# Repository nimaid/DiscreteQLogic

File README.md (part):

# DiscreteQLogic
My resources and projects relating to digital circuits made out of discrete transistors.

## Efficient Discrete NMOS Logic Gate Designs
I have yet to find a well-compiled source that lists the most efficient NMOS implementations using discrete MOSFETS and resistors. This is likely because, well, it's a very slow and outdated technology that draws more power than CMOS.

However, for DIY projects where one wishes to do the bare minimum of soldering, layout, and purchasing, NMOS provides very good functionality at about half the transistor count of CMOS (at the expense of adding some resistors). Therefore, I have decided to use NMOS for my DIY projects, and as such, I have been collecting the most efficient gate designs, which use fewest transistors and resistors possible.

*(I have been making a library of these parts for both Digital and LTspice, in order to simulate them before building them. You can find these libraries in their respective subfolders of this repository.)*

For this list, I will use some shorthand notation to refer to the total transistor and resistor counts for each part. This shorthand will follow the format `xQyR`, where `x` is the total transistor count and `y` is the total resistor count. So, for example, an XOR gate which was labeled `6Q3R` would require 6 transistors and 3 resistors to build.

Sometimes, you may see the part count listed in the format `(!aQbR/xQyR)`. This means the simplest (lowest part count) version of the part has it's input(s) or output(s) inverted (the `!` means `NOT` or inversion). *This inverted version uses `a` transistors and `b` resistors.* In order to use the part in it's non-inverted state, one or more NOT gates is needed, which increases the total component count per part. *This non-inverted version uses `x` transistors and `y` resistors.* If you are using many of these parts with a shared signal on their inputs (like a clock), it is more economical to invert that signal *once* before it then goes into each of the inverted variants of the part. In addition, sometimes you get inverted outputs for free (like with latches and flip-flops), so you actually don't even need NOT gates a lot of the time! This can save a *TON* of components when building things like multi-bit registers or enablers, where the savings add up with more bits.

Unless otherwise stated, all transistors are N-type.

Resistor values should be chosen based on acceptable power dissipation and speed requirements. If the resistors are large (on the order of 10kΩ+), then power dissipation will be very low (the resistor lets less current through to ground), but the response time of the gate will be much slower. This is due to an inherent weakness in NMOS where it takes longer to charge up the combined gate capacitance of the MOSFETs and the stray capacitance in the wires though a larger resistor. Conversely, smaller values will yield higher power usage, but faster response times.

### NOT (1Q1R)
<details>
<summary>Details</summary>

The simplest gate to construct is a NOT gate (also known as an inverter). This is simply a pullup resistor with a transistor configured to short the output to ground when voltage is applied to it's gate. Make sure you understand how this gate works, because this fundamental principal is the foundation which allows the systematic construction of every other NMOS gate.

</details>

#### This section must be re-written.
<details>
<summary>Show it to me anyway!</summary>

### NAND (2Q1R)
<details>
<summary>Details</summary>

The next step up in complexity is the NAND gate. This is essentially just a NOT gate with an extra transistor in series to ground. This has the effect of only shorting the output to ground if *both* transistors are conducting. This results in the behavior of a NAND gate.

</details>

### NOR (2Q1R)
<details>
<summary>Details</summary>

The NOR gate is almost exactly the same as the NAND gate, except the second transistor is connected in parallel as opposed to series. This has the effect of shorting the output to ground if *either* transistors are conducting. This results in the behavior of a NOR gate.

</details>

### n-way NAND and NOR (\{n\}Q1R)
<details>
<summary>Details</summary>

It is possible to efficiently make NAND and NOR gates that have more than 2 inputs without chaining together the above units. This method uses fewer transistors and resistors than simply chaining the 2-way gates together. We do this be applying the same logic that took us from a 1-way NOT gate to 2-way NAND and NOR gates, but instead of putting only 2 transistors in either series or parallel, we put `n` transistors, where `n` is the number of inputs we want.

Here is an 8-way NAND gate.

Here is an 8-way NOR gate.

</details>

### AND and OR (3Q2R)
<details>
<summary>Details</summary>

The best way to make AND and OR gates happens to be the most straightforward. All we have to do is add a NOT gate after the NAND and NOR gates, as shown.

AND:

OR:

</details>

### AOI[a-b-...] (\{a + b + ...\}Q1R)
<details>
<summary>Details</summary>

The AOI (And-Or-Invert) gate is a bit unusual at first glance, and it is not as well known as the other gates. However, it is essential for building efficient NMOS circuits. This gate acts on "sets" of inputs, and processes them as follows:
- It first runs each "set" of inputs through an `n`-way AND gate, where `n` is the number of inputs in that set.
- The results from all of the AND gates are run through an `m`-way OR gate, where `m` is the number of sets.
- Finally, the output of the OR gate is run through a NOT gate (also called an inverter).

AOI gates are defined by a series of numbers, which specify exactly how many sets of inputs there are, and how many inputs are in each set. Each set can have a different number of inputs, and you can have an many sets as you like. This is in the format `a-b-c-...`, where `a`, `b`, `c`, etc. specify how many inputs each set has, in order. So a `2-3-1` AOI gate would have 3 sets with 2 inputs going to the first AND gate, 3 inputs going to the second AND gate, and the third set has only 1 input that goes directly to the OR gate stage (because AND only makes sense with 2 or more inputs).

Here is an example of an AOI2-2 gate using conventional combinational logic.

So why do we care about this odd gate as a single unit? Why don't we just use combinations of AND and NOR gates whenever we need to do these types of operations? The answer is that all of these logical operations can be easily implemented in a single NMOS logic block that uses far fewer transistors and resistors to achieve the same behavior.

Here is that same AIO2-2 gate in NMOS logic, using 4Q1R.

The way this works is actually very clever. First, observe that this is still arranged with a pullup resistor and transistors that, with some combinations of inputs, shorts to ground. This is the same idea as the NOT gate, and this is where the "inversion" comes from.

Second, observe that there are 2 parallel paths to ground, just like the NOR gate. The only difference is that instead of a single transistor, each path has 2 transistors in series, which is exactly the same method used to construct the NAND gate. Indeed, when either set of series transistors is conducting, the output will be shorted to ground, providing the AND functionality for each set.

Finally, observe that because the sets of series transistors are in parallel with each other, the compound effect of ORing the results of the 2 AND operations is realized.

Here is an example of a 2-1 AOI gate.

And just to make sure it makes sense, here is a 2-2-2-2 AOI gate.

As you can see, you can customize the number of sets and their respective input count to fit your specific needs in the same way you can customize the number of inputs to a NAND or NOR gate.

The final transistor count of each AOI gate will be exactly equal to the total number of inputs, and each AOI gate will only ever use a single resistor.

</details>

### XOR (6Q3R)
<details>
<summary>Details</summary>

It is possible to use an AOI2-2 gate and 2 NOT gates to make an extremely elegant XOR gate, as shown below.

To understand why this works, think about the AOI gate as "a gate that will set it's output to 0 only when a set of inputs is all 1". In this way, we can analyze the truth table of the XOR gate to find which input conditions result in a 0 and test for them with sets of AND gates that have their inputs set to 1 in those conditions.

XOR gate truth table:
```
┌───┬───┬─────┐
│ A │ B │ Out │
╞═══╪═══╪═════╡
│ 0 │ 0 │  0  │
├───┼───┼─────┤
│ 0 │ 1 │  1  │
├───┼───┼─────┤
│ 1 │ 0 │  1  │
├───┼───┼─────┤
│ 1 │ 1 │  0  │
└───┴───┴─────┘
```

We can see that the output is only 0 when both inputs are the same. Therefore, the first AND gate in the AOI2-2 is fed with both inputs directly, so that the output will go to 0 when both inputs are 1. Next, we need the output to also be 0 when both inputs are 0, and we can do this by simply inverting both inputs before feeding them into the second AND gate. Now we have a gate that outputs 0 when the inputs are either both 1 or both 0, and outputs 1 otherwise. This is an XOR gate!

</details>

### XNOR (6Q3R)
<details>
<summary>Details</summary>

We can implement the XNOR gate without using the classic XOR + NOT gate setup. To do so, we simply re-order the NOT gates in our XOR gate design so that the output goes to 0 in each case where the inputs are different, as opposed to the same.

</details>

### Enabler / 3-State Driver (!5Q1R/6Q2R)
<details>
<summary>Details</summary>

This component is a bit unique, as it is the only one which *requires* a few P-channel MOSFETs in addition to N-channel ones. This circuit takes 2 inputs, `In` (input) and `en` (enable). When `en` is 1, the output is equal to `In`. However, when `en` is 0, the output is in a state known as "high impedance". This is a state that is neither a 0 (ground) or 1 (VCC), but instead the output is electrically disconnected entirely.

This is extremely useful when you want to have 2 signals occupy the same wire at different times (the most common example being a data bus inside a computer). To understand the reason why we need a special part for this, lets take an example case where we connect the outputs of 2 AND gates to each other directly. If the first was outputting 1 (VCC) and the second was outputting 0 (ground), then there would be a short-circuit through that wire and those 2 AND gates, which would cause the device to malfunction and likely sustain damage. By putting enablers between the outputs and their shared wire, and by *only enabling a single output at a time*, you can avoid such a disaster.

Before showing you the enabler circuit, it will be useful to first understand how a CMOS-based NOT gate works:

The top transistor is P-channel, and the bottom one is N-channel. In the configuration shown, the N-channel MOSFET will conduct (to ground) when VCC (1) is applied to it's gate, and will act like an open switch when it is grounded (0). This works just like in the N-channel NOT gate. However, the P-channel MOSFET behaves in exactly the opposite way. When VCC (1) is applied to it's gate, it acts like an open switch, and it conducts (to VCC) when the gate is grounded (0).

With this understanding, we can see that when `In` is 0, the upper P-channel MOSFET will be conducting to VCC (1), and the lower N-channel MOSFET will be disconnected, resulting in `Out` being only connected to VCC, and therefore a 1. Conversely, when `In` is 1, the P-channel MOSFET will be open and the N-channel one will be conducting to ground, therefore resulting in a 0. This is the fundamental idea behind CMOS, and it is used in the construction of the enabler circuit.

Now, we are ready to look at the *inverted* enabler circuit (5Q1R):

The top 2 transistors are P-channel, while the lower two are N-channel. *(This means the circuit uses 3 N-channel MOSFETs and 2 P-channel MOSFETs.)*

First, note how to topmost (P-channel) and bottommost (N-channel) MOSFETs both have their gates connected directly to `In`, just like the CMOS NOT gate. This means that if those other 2 MOSFETs weren't in the way, this circuit would actually *be* a CMOS NOT gate, and would therefore just invert the input signal. (Out = !In) Alone this isn't very special, but those 2 MOSFETs in the middle which seperate these ones from `Out` are what actually make this circuit useful as an enabler.

Those 2 middle MOSFETs are also a P-channel/N-channel pair, but with a single critical change from the CMOS NOT gate. Instead of both of their gates being directly connected, the upper-middle P-channel MOSFET has it's gate input inverted by a NOT gate. This means that when `en` is 1, *both* MOSFETs will conduct, but when `In` is 0, *neither* MOSFET will conduct (both act like an open switch). This means that when `en` is 1, the effect of the topmost and bottommost MOSFETs are uninterrupted and `Out` is equal to `!In`. However, when `en` is 0, `Out` is completely disconnected from both VCC and ground, *regardless* of the state of topmost and bottommost MOSFETs. This results in the desired behavior of an enabler, but with the input inverted.

In situations where an inverted input signal is already available without adding a NOT gate (like the inverted output on a latch or flip-flop), you can simply use this inverted version of the enabler and remove a few components from the design. However, there are often times where you can' get away with that, and absolutely need an enabler with a non-inverted input. In these situations, you have to bite the bullet and add a NOT gate, as shown below.

Non-inverted Enabler (6Q2R):

</details>

### Multiplexer (!5Q2R/6Q3R) [WIP] 
<details>
<summary>Details</summary>

[TODO: Explain the MUX API and why it is useful for routing signals.]

This functionality can be accomplished with the following combinational logic:

[TODO: Explain how the AND gates only allow the respective `In` signal through if the other input to the AND gate is on. Explain that because of the NOT gate, only 1 of the AND gates will allow it's signal to pass to the OR gate, effectively discarding the signal not selected by `sel`. Note how because only 1 signal is let through, the output of the OR gate will be equal to the selected signal, which is the desired behavior.]

Here is an efficient implementation of a multiplexer *with an inverted output* using an AOI2-2 gate (5Q2R):

Note that the AOI2-2 gate is almost exactly what we nee to replace the 2 AND gates and 1 OR gate. The only issue is that the output of the OR gate is inverted. Sometimes you can leverage the inverting nature of this circuit to avoid using a NOT gate to invert the inputs/output. However, if you need a non-inverting multiplexer, you must use a NOT gate on the output, as shown (6Q3R):

</details>

### Demultiplexer (!5Q3R/6Q4R) [WIP]
<details>
<summary>Details</summary>

[TODO]

[TODO]

[TODO]

</details>

### RS Latch and SR Latch (4Q2R) [WIP]
<details>
<summary>Details</summary>

The RS latch is the basic form of memory. [TODO: Add API definition and explain why it's useful.]

RS Latch Diagram:

[TODO: Add a breakdown of why it works, step-by step. Also explain metastable (invalid) configurations. Also explain that the circuit starts up in a "random" state.]

Here is the RS latch in the logic simulator, using our NMOS components:

The SR latch is very similar to the RS latch, but it is made of NAND gates instead of NOR gates. In addition, it's inputs are both inverted (active low) and flipped (set on top and reset on bottom). [TODO: Add full API definition and explain why it's useful, especially compared to the RS latch. Note now the inverted inputs are actually useful later on.]

SR Latch Diagram:

[TODO: Add a step-by-step breakdown that references the RS latch breakdown. Explain that this also starts up in a "random" state.]

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
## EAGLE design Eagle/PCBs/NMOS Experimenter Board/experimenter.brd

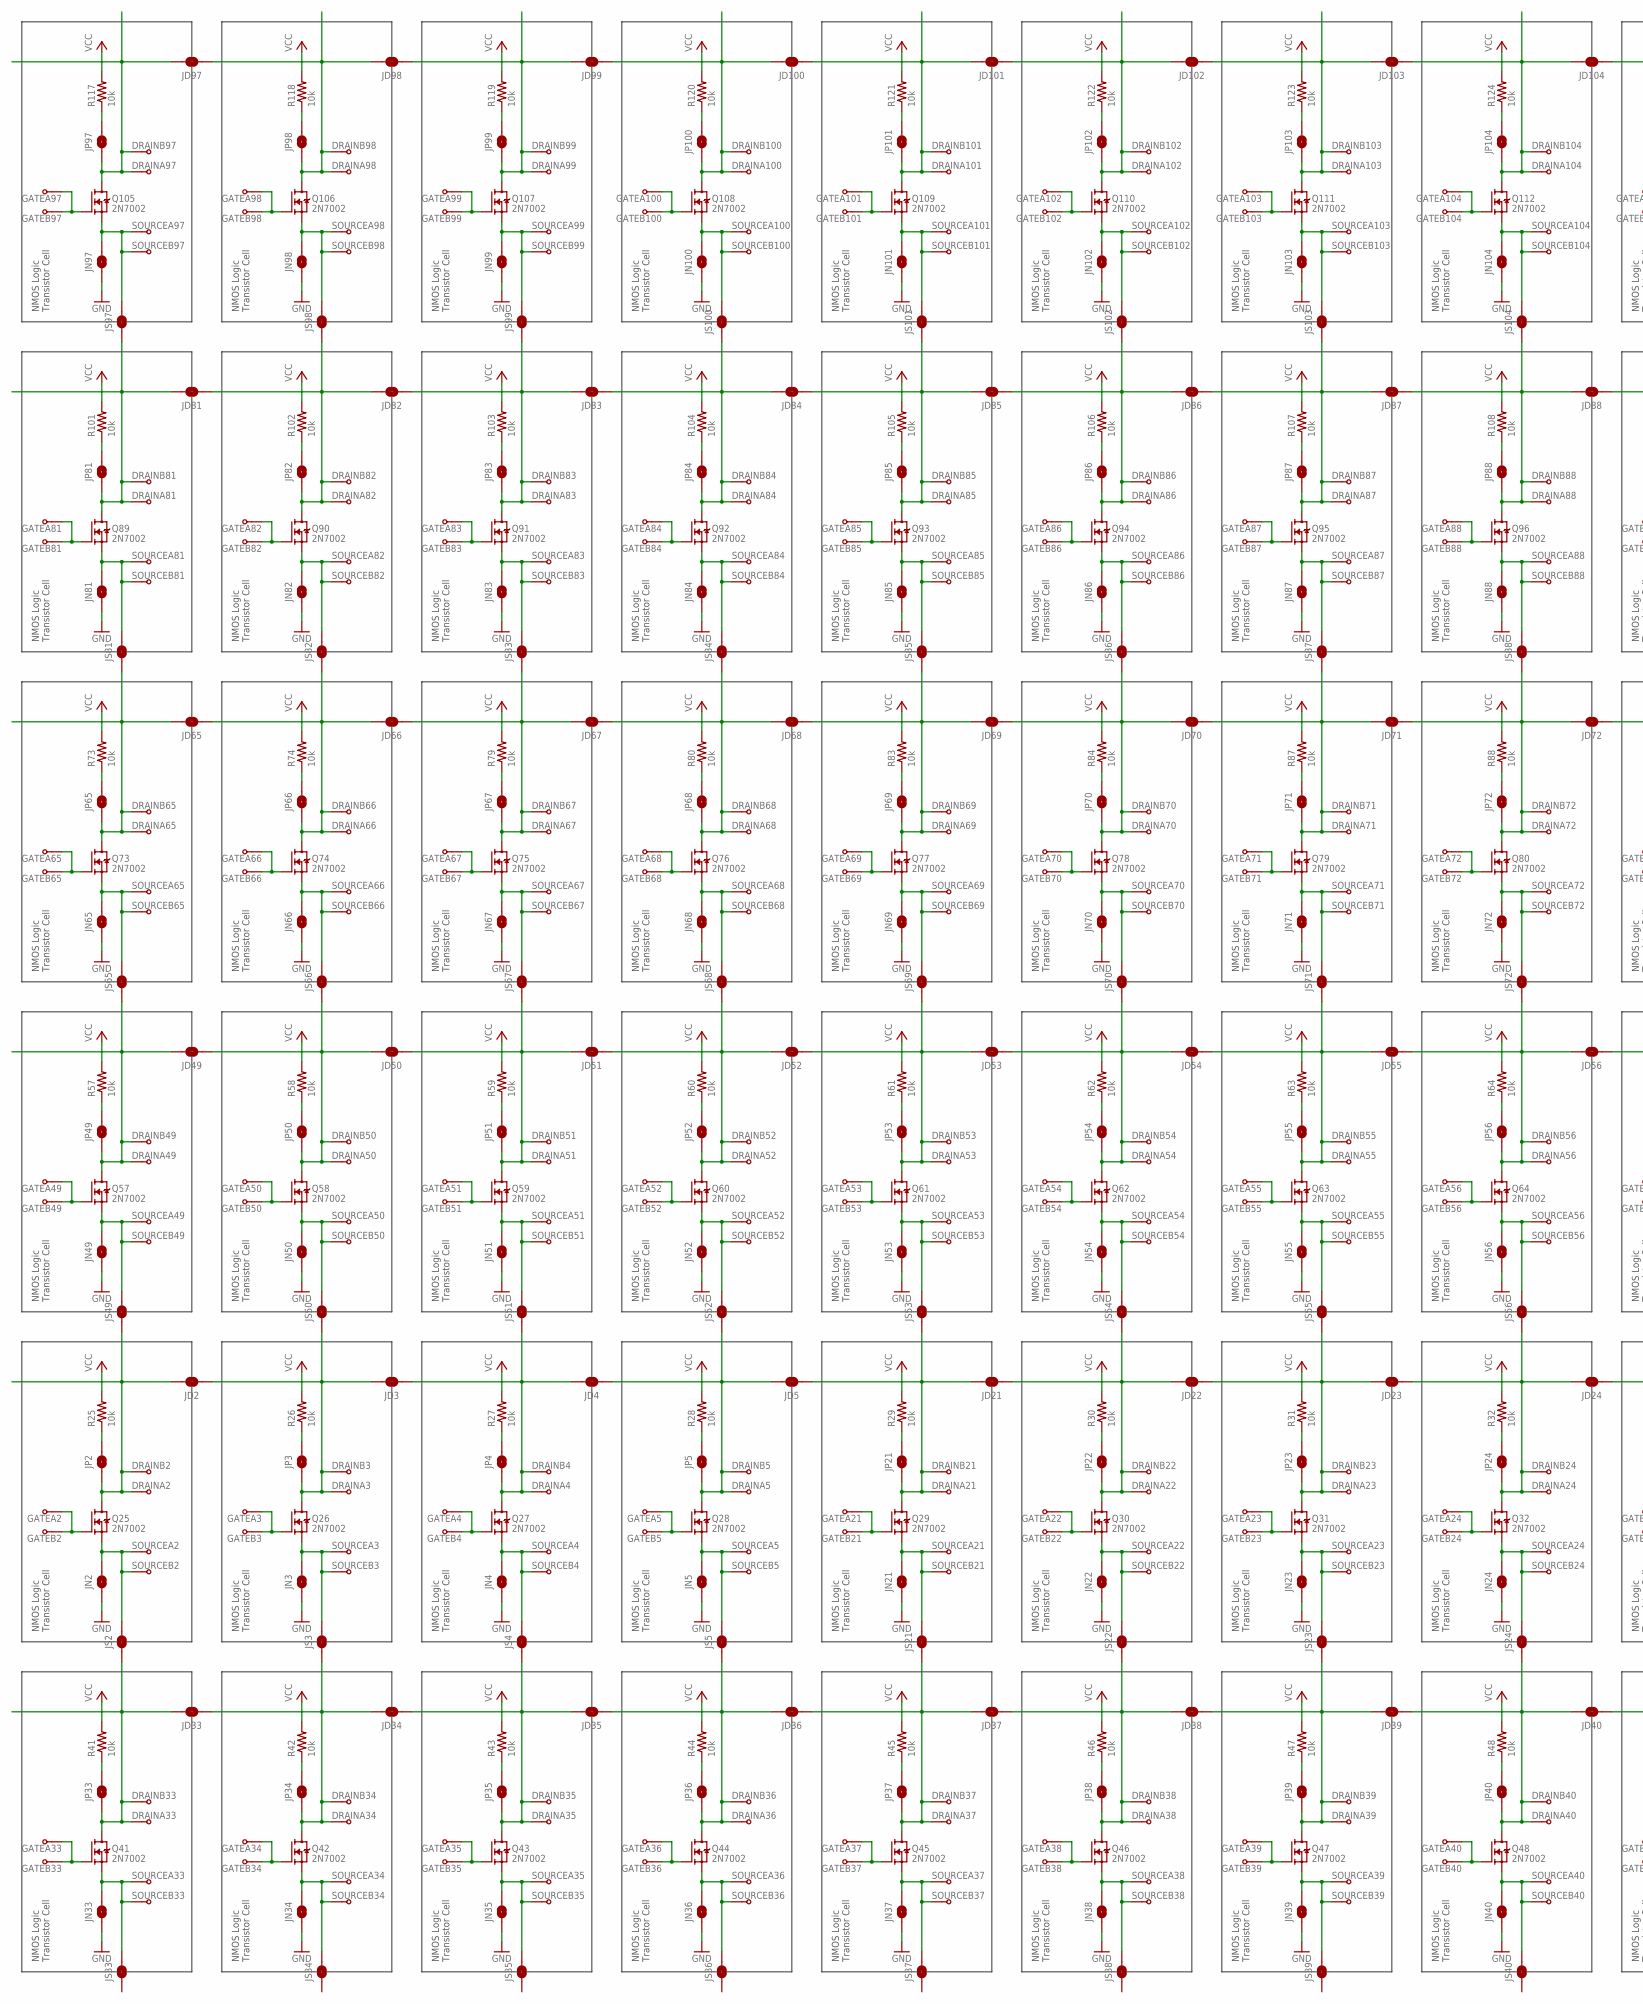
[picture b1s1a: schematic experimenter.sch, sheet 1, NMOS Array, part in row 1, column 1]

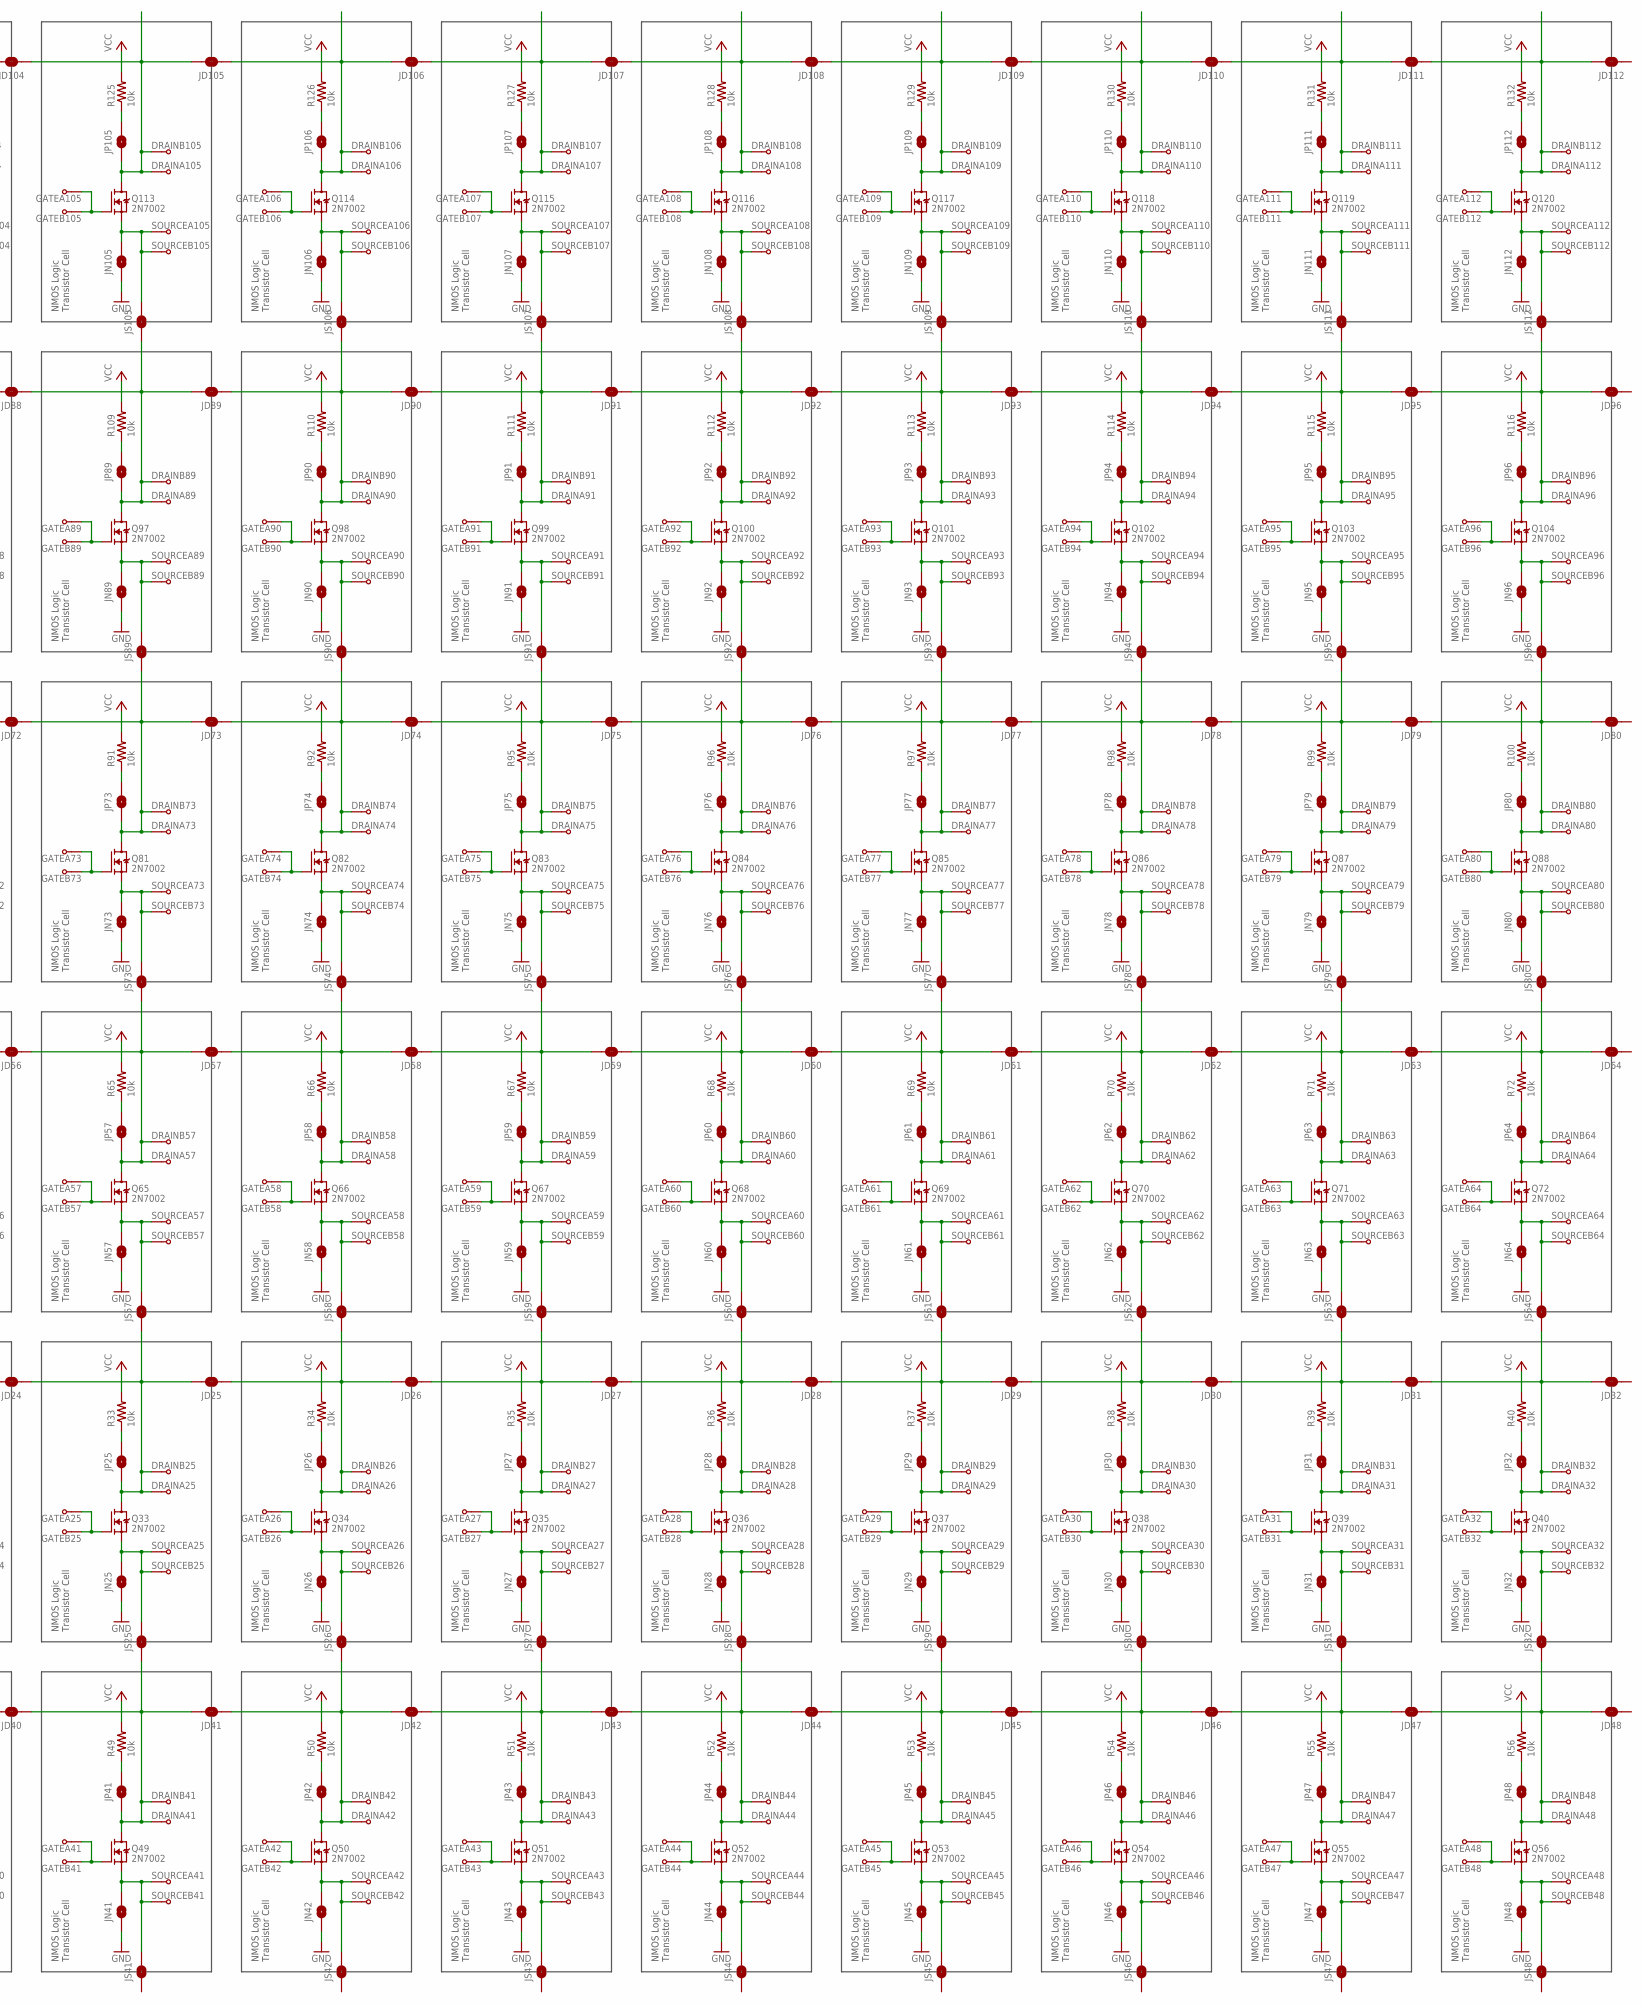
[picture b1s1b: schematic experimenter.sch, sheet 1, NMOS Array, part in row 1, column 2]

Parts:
DRAINA2, DRAINA3, DRAINA4, DRAINA5, DRAINA21, DRAINA22, DRAINA23, DRAINA24, DRAINA25, DRAINA26, DRAINA27, DRAINA28, DRAINA29, DRAINA30, DRAINA31, DRAINA32, DRAINA33, DRAINA34, DRAINA35, DRAINA36, DRAINA37, DRAINA38, DRAINA39, DRAINA40, DRAINA41, DRAINA42, DRAINA43, DRAINA44, DRAINA45, DRAINA46, DRAINA47, DRAINA48, DRAINA49, DRAINA50, DRAINA51, DRAINA52, DRAINA53, DRAINA54, DRAINA55, DRAINA56, DRAINA57, DRAINA58, DRAINA59, DRAINA60, DRAINA61, DRAINA62, DRAINA63, DRAINA64, DRAINA65, DRAINA66, DRAINA67, DRAINA68, DRAINA69, DRAINA70, DRAINA71, DRAINA72, DRAINA73, DRAINA74, DRAINA75, DRAINA76, DRAINA77, DRAINA78, DRAINA79, DRAINA80, DRAINA81, DRAINA82, DRAINA83, DRAINA84, DRAINA85, DRAINA86, DRAINA87, DRAINA88, DRAINA89, DRAINA90, DRAINA91, DRAINA92, DRAINA93, DRAINA94, DRAINA95, DRAINA96, DRAINA97, DRAINA98, DRAINA99, DRAINA100, DRAINA101, DRAINA102, DRAINA103, DRAINA104, DRAINA105, DRAINA106, DRAINA107, DRAINA108, DRAINA109, DRAINA110, DRAINA111, DRAINA112: TPTHT; PROTOPAD-THT-PAD
DRAINB2, DRAINB3, DRAINB4, DRAINB5, DRAINB21, DRAINB22, DRAINB23, DRAINB24, DRAINB25, DRAINB26, DRAINB27, DRAINB28, DRAINB29, DRAINB30, DRAINB31, DRAINB32, DRAINB33, DRAINB34, DRAINB35, DRAINB36, DRAINB37, DRAINB38, DRAINB39, DRAINB40, DRAINB41, DRAINB42, DRAINB43, DRAINB44, DRAINB45, DRAINB46, DRAINB47, DRAINB48, DRAINB49, DRAINB50, DRAINB51, DRAINB52, DRAINB53, DRAINB54, DRAINB55, DRAINB56, DRAINB57, DRAINB58, DRAINB59, DRAINB60, DRAINB61, DRAINB62, DRAINB63, DRAINB64, DRAINB65, DRAINB66, DRAINB67, DRAINB68, DRAINB69, DRAINB70, DRAINB71, DRAINB72, DRAINB73, DRAINB74, DRAINB75, DRAINB76, DRAINB77, DRAINB78, DRAINB79, DRAINB80, DRAINB81, DRAINB82, DRAINB83, DRAINB84, DRAINB85, DRAINB86, DRAINB87, DRAINB88, DRAINB89, DRAINB90, DRAINB91, DRAINB92, DRAINB93, DRAINB94, DRAINB95, DRAINB96, DRAINB97, DRAINB98, DRAINB99, DRAINB100, DRAINB101, DRAINB102, DRAINB103, DRAINB104, DRAINB105, DRAINB106, DRAINB107, DRAINB108, DRAINB109, DRAINB110, DRAINB111, DRAINB112: TPTHT; PROTOPAD-THT-PAD
GATEA2, GATEA3, GATEA4, GATEA5, GATEA21, GATEA22, GATEA23, GATEA24, GATEA25, GATEA26, GATEA27, GATEA28, GATEA29, GATEA30, GATEA31, GATEA32, GATEA33, GATEA34, GATEA35, GATEA36, GATEA37, GATEA38, GATEA39, GATEA40, GATEA41, GATEA42, GATEA43, GATEA44, GATEA45, GATEA46, GATEA47, GATEA48, GATEA49, GATEA50, GATEA51, GATEA52, GATEA53, GATEA54, GATEA55, GATEA56, GATEA57, GATEA58, GATEA59, GATEA60, GATEA61, GATEA62, GATEA63, GATEA64, GATEA65, GATEA66, GATEA67, GATEA68, GATEA69, GATEA70, GATEA71, GATEA72, GATEA73, GATEA74, GATEA75, GATEA76, GATEA77, GATEA78, GATEA79, GATEA80, GATEA81, GATEA82, GATEA83, GATEA84, GATEA85, GATEA86, GATEA87, GATEA88, GATEA89, GATEA90, GATEA91, GATEA92, GATEA93, GATEA94, GATEA95, GATEA96, GATEA97, GATEA98, GATEA99, GATEA100, GATEA101, GATEA102, GATEA103, GATEA104, GATEA105, GATEA106, GATEA107, GATEA108, GATEA109, GATEA110, GATEA111, GATEA112: TPTHT; PROTOPAD-THT-PAD
GATEB2, GATEB3, GATEB4, GATEB5, GATEB21, GATEB22, GATEB23, GATEB24, GATEB25, GATEB26, GATEB27, GATEB28, GATEB29, GATEB30, GATEB31, GATEB32, GATEB33, GATEB34, GATEB35, GATEB36, GATEB37, GATEB38, GATEB39, GATEB40, GATEB41, GATEB42, GATEB43, GATEB44, GATEB45, GATEB46, GATEB47, GATEB48, GATEB49, GATEB50, GATEB51, GATEB52, GATEB53, GATEB54, GATEB55, GATEB56, GATEB57, GATEB58, GATEB59, GATEB60, GATEB61, GATEB62, GATEB63, GATEB64, GATEB65, GATEB66, GATEB67, GATEB68, GATEB69, GATEB70, GATEB71, GATEB72, GATEB73, GATEB74, GATEB75, GATEB76, GATEB77, GATEB78, GATEB79, GATEB80, GATEB81, GATEB82, GATEB83, GATEB84, GATEB85, GATEB86, GATEB87, GATEB88, GATEB89, GATEB90, GATEB91, GATEB92, GATEB93, GATEB94, GATEB95, GATEB96, GATEB97, GATEB98, GATEB99, GATEB100, GATEB101, GATEB102, GATEB103, GATEB104, GATEB105, GATEB106, GATEB107, GATEB108, GATEB109, GATEB110, GATEB111, GATEB112: TPTHT; PROTOPAD-THT-PAD
JD2, JD3, JD4, JD5, JD21, JD22, JD23, JD24, JD25, JD26, JD27, JD28, JD29, JD30, JD31, JD32, JD33, JD34, JD35, JD36, JD37, JD38, JD39, JD40, JD41, JD42, JD43, JD44, JD45, JD46, JD47, JD48, JD49, JD50, JD51, JD52, JD53, JD54, JD55, JD56, JD57, JD58, JD59, JD60, JD61, JD62, JD63, JD64, JD65, JD66, JD67, JD68, JD69, JD70, JD71, JD72, JD73, JD74, JD75, JD76, JD77, JD78, JD79, JD80, JD81, JD82, JD83, JD84, JD85, JD86, JD87, JD88, JD89, JD90, JD91, JD92, JD93, JD94, JD95, JD96, JD97, JD98, JD99, JD100, JD101, JD102, JD103, JD104, JD105, JD106, JD107, JD108, JD109, JD110, JD111, JD112: SJ_NO_THIN; SJ_2S-NO-THIN
JN2, JN3, JN4, JN5, JN21, JN22, JN23, JN24, JN25, JN26, JN27, JN28, JN29, JN30, JN31, JN32, JN33, JN34, JN35, JN36, JN37, JN38, JN39, JN40, JN41, JN42, JN43, JN44, JN45, JN46, JN47, JN48, JN49, JN50, JN51, JN52, JN53, JN54, JN55, JN56, JN57, JN58, JN59, JN60, JN61, JN62, JN63, JN64, JN65, JN66, JN67, JN68, JN69, JN70, JN71, JN72, JN73, JN74, JN75, JN76, JN77, JN78, JN79, JN80, JN81, JN82, JN83, JN84, JN85, JN86, JN87, JN88, JN89, JN90, JN91, JN92, JN93, JN94, JN95, JN96, JN97, JN98, JN99, JN100, JN101, JN102, JN103, JN104, JN105, JN106, JN107, JN108, JN109, JN110, JN111, JN112: SJ_NO_THIN; SJ_2S-NO-THIN
JP2, JP3, JP4, JP5, JP21, JP22, JP23, JP24, JP25, JP26, JP27, JP28, JP29, JP30, JP31, JP32, JP33, JP34, JP35, JP36, JP37, JP38, JP39, JP40, JP41, JP42, JP43, JP44, JP45, JP46, JP47, JP48, JP49, JP50, JP51, JP52, JP53, JP54, JP55, JP56, JP57, JP58, JP59, JP60, JP61, JP62, JP63, JP64, JP65, JP66, JP67, JP68, JP69, JP70, JP71, JP72, JP73, JP74, JP75, JP76, JP77, JP78, JP79, JP80, JP81, JP82, JP83, JP84, JP85, JP86, JP87, JP88, JP89, JP90, JP91, JP92, JP93, JP94, JP95, JP96, JP97, JP98, JP99, JP100, JP101, JP102, JP103, JP104, JP105, JP106, JP107, JP108, JP109, JP110, JP111, JP112: SJ_NO_THIN; SJ_2S-NO-THIN
JS2, JS3, JS4, JS5, JS21, JS22, JS23, JS24, JS25, JS26, JS27, JS28, JS29, JS30, JS31, JS32, JS33, JS34, JS35, JS36, JS37, JS38, JS39, JS40, JS41, JS42, JS43, JS44, JS45, JS46, JS47, JS48, JS49, JS50, JS51, JS52, JS53, JS54, JS55, JS56, JS57, JS58, JS59, JS60, JS61, JS62, JS63, JS64, JS65, JS66, JS67, JS68, JS69, JS70, JS71, JS72, JS73, JS74, JS75, JS76, JS77, JS78, JS79, JS80, JS81, JS82, JS83, JS84, JS85, JS86, JS87, JS88, JS89, JS90, JS91, JS92, JS93, JS94, JS95, JS96, JS97, JS98, JS99, JS100, JS101, JS102, JS103, JS104, JS105, JS106, JS107, JS108, JS109, JS110, JS111, JS112: SJ_NO_THIN; SJ_2S-NO-THIN
Q25, Q26, Q27, Q28, Q29, Q30, Q31, Q32, Q33, Q34, Q35, Q36, Q37, Q38, Q39, Q40, Q41, Q42, Q43, Q44, Q45, Q46, Q47, Q48, Q49, Q50, Q51, Q52, Q53, Q54, Q55, Q56, Q57, Q58, Q59, Q60, Q61, Q62, Q63, Q64, Q65, Q66, Q67, Q68, Q69, Q70, Q71, Q72, Q73, Q74, Q75, Q76, Q77, Q78, Q79, Q80, Q81, Q82, Q83, Q84, Q85, Q86, Q87, Q88, Q89, Q90, Q91, Q92, Q93, Q94, Q95, Q96, Q97, Q98, Q99, Q100, Q101, Q102, Q103, Q104, Q105, Q106, Q107, Q108, Q109, Q110, Q111, Q112, Q113, Q114, Q115, Q116, Q117, Q118, Q119, Q120: 2N7002; SOT23
R25, R26, R27, R28, R29, R30, R31, R32, R33, R34, R35, R36, R37, R38, R39, R40, R41, R42, R43, R44, R45, R46, R47, R48, R49, R50, R51, R52, R53, R54, R55, R56, R57, R58, R59, R60, R61, R62, R63, R64, R65, R66, R67, R68, R69, R70, R71, R72, R73, R74, R79, R80, R83, R84, R87, R88, R91, R92, R95, R96, R97, R98, R99, R100, R101, R102, R103, R104, R105, R106, R107, R108, R109, R110, R111, R112, R113, R114, R115, R116, R117, R118, R119, R120, R121, R122, R123, R124, R125, R126, R127, R128, R129, R130, R131, R132: 10k; R0603
SOURCEA2, SOURCEA3, SOURCEA4, SOURCEA5, SOURCEA21, SOURCEA22, SOURCEA23, SOURCEA24, SOURCEA25, SOURCEA26, SOURCEA27, SOURCEA28, SOURCEA29, SOURCEA30, SOURCEA31, SOURCEA32, SOURCEA33, SOURCEA34, SOURCEA35, SOURCEA36, SOURCEA37, SOURCEA38, SOURCEA39, SOURCEA40, SOURCEA41, SOURCEA42, SOURCEA43, SOURCEA44, SOURCEA45, SOURCEA46, SOURCEA47, SOURCEA48, SOURCEA49, SOURCEA50, SOURCEA51, SOURCEA52, SOURCEA53, SOURCEA54, SOURCEA55, SOURCEA56, SOURCEA57, SOURCEA58, SOURCEA59, SOURCEA60, SOURCEA61, SOURCEA62, SOURCEA63, SOURCEA64, SOURCEA65, SOURCEA66, SOURCEA67, SOURCEA68, SOURCEA69, SOURCEA70, SOURCEA71, SOURCEA72, SOURCEA73, SOURCEA74, SOURCEA75, SOURCEA76, SOURCEA77, SOURCEA78, SOURCEA79, SOURCEA80, SOURCEA81, SOURCEA82, SOURCEA83, SOURCEA84, SOURCEA85, SOURCEA86, SOURCEA87, SOURCEA88, SOURCEA89, SOURCEA90, SOURCEA91, SOURCEA92, SOURCEA93, SOURCEA94, SOURCEA95, SOURCEA96, SOURCEA97, SOURCEA98, SOURCEA99, SOURCEA100, SOURCEA101, SOURCEA102, SOURCEA103, SOURCEA104, SOURCEA105, SOURCEA106, SOURCEA107, SOURCEA108, SOURCEA109, SOURCEA110, SOURCEA111, SOURCEA112: TPTHT; PROTOPAD-THT-PAD
SOURCEB2, SOURCEB3, SOURCEB4, SOURCEB5, SOURCEB21, SOURCEB22, SOURCEB23, SOURCEB24, SOURCEB25, SOURCEB26, SOURCEB27, SOURCEB28, SOURCEB29, SOURCEB30, SOURCEB31, SOURCEB32, SOURCEB33, SOURCEB34, SOURCEB35, SOURCEB36, SOURCEB37, SOURCEB38, SOURCEB39, SOURCEB40, SOURCEB41, SOURCEB42, SOURCEB43, SOURCEB44, SOURCEB45, SOURCEB46, SOURCEB47, SOURCEB48, SOURCEB49, SOURCEB50, SOURCEB51, SOURCEB52, SOURCEB53, SOURCEB54, SOURCEB55, SOURCEB56, SOURCEB57, SOURCEB58, SOURCEB59, SOURCEB60, SOURCEB61, SOURCEB62, SOURCEB63, SOURCEB64, SOURCEB65, SOURCEB66, SOURCEB67, SOURCEB68, SOURCEB69, SOURCEB70, SOURCEB71, SOURCEB72, SOURCEB73, SOURCEB74, SOURCEB75, SOURCEB76, SOURCEB77, SOURCEB78, SOURCEB79, SOURCEB80, SOURCEB81, SOURCEB82, SOURCEB83, SOURCEB84, SOURCEB85, SOURCEB86, SOURCEB87, SOURCEB88, SOURCEB89, SOURCEB90, SOURCEB91, SOURCEB92, SOURCEB93, SOURCEB94, SOURCEB95, SOURCEB96, SOURCEB97, SOURCEB98, SOURCEB99, SOURCEB100, SOURCEB101, SOURCEB102, SOURCEB103, SOURCEB104, SOURCEB105, SOURCEB106, SOURCEB107, SOURCEB108, SOURCEB109, SOURCEB110, SOURCEB111, SOURCEB112: TPTHT; PROTOPAD-THT-PAD

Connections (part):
GND: JN2.1, JN3.1, JN4.1, JN5.1, JN21.1, JN22.1, JN23.1, JN24.1, JN25.1, JN26.1, JN27.1, JN28.1, JN29.1, JN30.1, JN31.1, JN32.1, JN33.1, JN34.1, JN35.1, JN36.1, JN37.1, JN38.1, JN39.1, JN40.1, JN41.1, JN42.1, JN43.1, JN44.1, JN45.1, JN46.1, JN47.1, JN48.1, JN49.1, JN50.1, JN51.1, JN52.1, JN53.1, JN54.1, JN55.1, JN56.1, JN57.1, JN58.1, JN59.1, JN60.1, JN61.1, JN62.1, JN63.1, JN64.1, JN65.1, JN66.1, JN67.1, JN68.1, JN69.1, JN70.1, JN71.1, JN72.1, JN73.1, JN74.1, JN75.1, JN76.1, JN77.1, JN78.1, JN79.1, JN80.1, JN81.1, JN82.1, JN83.1, JN84.1, JN85.1, JN86.1, JN87.1, JN88.1, JN89.1, JN90.1, JN91.1, JN92.1, JN93.1, JN94.1, JN95.1, JN96.1, JN97.1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; also elsewhere on the board
unnamed: JP2.2, R25.1
unnamed: JN2.2, JS2.2, Q25.2 (S), SOURCEA2.P1, SOURCEB2.P1
unnamed: DRAINA2.P1, DRAINB2.P1, JD2.2, JP2.1, JS49.1, Q25.3 (D)
unnamed: GATEA2.P1, GATEB2.P1, Q25.1 (G)
unnamed: JP3.2, R26.1
unnamed: JN3.2, JS3.2, Q26.2 (S), SOURCEA3.P1, SOURCEB3.P1
unnamed: DRAINA3.P1, DRAINB3.P1, JD2.1, JD3.2, JP3.1, JS50.1, Q26.3 (D)
unnamed: GATEA3.P1, GATEB3.P1, Q26.1 (G)
unnamed: JP4.2, R27.1
unnamed: JN4.2, JS4.2, Q27.2 (S), SOURCEA4.P1, SOURCEB4.P1
unnamed: DRAINA4.P1, DRAINB4.P1, JD3.1, JD4.2, JP4.1, JS51.1, Q27.3 (D)
unnamed: GATEA4.P1, GATEB4.P1, Q27.1 (G)
unnamed: JP5.2, R28.1
unnamed: JN5.2, JS5.2, Q28.2 (S), SOURCEA5.P1, SOURCEB5.P1
unnamed: DRAINA5.P1, DRAINB5.P1, JD4.1, JD5.2, JP5.1, JS52.1, Q28.3 (D)
unnamed: GATEA5.P1, GATEB5.P1, Q28.1 (G)
unnamed: JP21.2, R29.1
unnamed: JN21.2, JS21.2, Q29.2 (S), SOURCEA21.P1, SOURCEB21.P1
unnamed: DRAINA21.P1, DRAINB21.P1, JD5.1, JD21.2, JP21.1, JS53.1, Q29.3 (D)
unnamed: GATEA21.P1, GATEB21.P1, Q29.1 (G)
unnamed: JP22.2, R30.1
unnamed: JN22.2, JS22.2, Q30.2 (S), SOURCEA22.P1, SOURCEB22.P1
unnamed: DRAINA22.P1, DRAINB22.P1, JD21.1, JD22.2, JP22.1, JS54.1, Q30.3 (D)
unnamed: GATEA22.P1, GATEB22.P1, Q30.1 (G)
unnamed: JP23.2, R31.1
unnamed: JN23.2, JS23.2, Q31.2 (S), SOURCEA23.P1, SOURCEB23.P1
unnamed: DRAINA23.P1, DRAINB23.P1, JD22.1, JD23.2, JP23.1, JS55.1, Q31.3 (D)
unnamed: GATEA23.P1, GATEB23.P1, Q31.1 (G)
unnamed: JP24.2, R32.1
unnamed: JN24.2, JS24.2, Q32.2 (S), SOURCEA24.P1, SOURCEB24.P1
unnamed: DRAINA24.P1, DRAINB24.P1, JD23.1, JD24.2, JP24.1, JS56.1, Q32.3 (D)
unnamed: GATEA24.P1, GATEB24.P1, Q32.1 (G)
unnamed: JP25.2, R33.1
unnamed: JN25.2, JS25.2, Q33.2 (S), SOURCEA25.P1, SOURCEB25.P1
unnamed: DRAINA25.P1, DRAINB25.P1, JD24.1, JD25.2, JP25.1, JS57.1, Q33.3 (D)
unnamed: GATEA25.P1, GATEB25.P1, Q33.1 (G)
unnamed: JP26.2, R34.1
unnamed: JN26.2, JS26.2, Q34.2 (S), SOURCEA26.P1, SOURCEB26.P1
unnamed: DRAINA26.P1, DRAINB26.P1, JD25.1, JD26.2, JP26.1, JS58.1, Q34.3 (D)
unnamed: GATEA26.P1, GATEB26.P1, Q34.1 (G)
unnamed: JP27.2, R35.1
unnamed: JN27.2, JS27.2, Q35.2 (S), SOURCEA27.P1, SOURCEB27.P1
unnamed: DRAINA27.P1, DRAINB27.P1, JD26.1, JD27.2, JP27.1, JS59.1, Q35.3 (D)
unnamed: GATEA27.P1, GATEB27.P1, Q35.1 (G)
unnamed: JP28.2, R36.1
unnamed: JN28.2, JS28.2, Q36.2 (S), SOURCEA28.P1, SOURCEB28.P1
unnamed: DRAINA28.P1, DRAINB28.P1, JD27.1, JD28.2, JP28.1, JS60.1, Q36.3 (D)
unnamed: GATEA28.P1, GATEB28.P1, Q36.1 (G)
unnamed: JP29.2, R37.1
unnamed: JN29.2, JS29.2, Q37.2 (S), SOURCEA29.P1, SOURCEB29.P1
unnamed: DRAINA29.P1, DRAINB29.P1, JD28.1, JD29.2, JP29.1, JS61.1, Q37.3 (D)
unnamed: GATEA29.P1, GATEB29.P1, Q37.1 (G)
unnamed: JP30.2, R38.1
unnamed: JN30.2, JS30.2, Q38.2 (S), SOURCEA30.P1, SOURCEB30.P1
unnamed: DRAINA30.P1, DRAINB30.P1, JD29.1, JD30.2, JP30.1, JS62.1, Q38.3 (D)
unnamed: GATEA30.P1, GATEB30.P1, Q38.1 (G)
unnamed: JP31.2, R39.1
unnamed: JN31.2, JS31.2, Q39.2 (S), SOURCEA31.P1, SOURCEB31.P1
unnamed: DRAINA31.P1, DRAINB31.P1, JD30.1, JD31.2, JP31.1, JS63.1, Q39.3 (D)
unnamed: GATEA31.P1, GATEB31.P1, Q39.1 (G)
unnamed: JP32.2, R40.1
unnamed: JN32.2, JS32.2, Q40.2 (S), SOURCEA32.P1, SOURCEB32.P1
unnamed: DRAINA32.P1, DRAINB32.P1, JD31.1, JD32.2, JP32.1, JS64.1, Q40.3 (D)
unnamed: GATEA32.P1, GATEB32.P1, Q40.1 (G)
unnamed: JP33.2, R41.1
unnamed: JN33.2, JS33.2, Q41.2 (S), SOURCEA33.P1, SOURCEB33.P1
unnamed: DRAINA33.P1, DRAINB33.P1, JD33.2, JP33.1, JS2.1, Q41.3 (D)
unnamed: GATEA33.P1, GATEB33.P1, Q41.1 (G)
unnamed: JP34.2, R42.1
unnamed: JN34.2, JS34.2, Q42.2 (S), SOURCEA34.P1, SOURCEB34.P1
unnamed: DRAINA34.P1, DRAINB34.P1, JD33.1, JD34.2, JP34.1, JS3.1, Q42.3 (D)
unnamed: GATEA34.P1, GATEB34.P1, Q42.1 (G)
unnamed: JP35.2, R43.1
unnamed: JN35.2, JS35.2, Q43.2 (S), SOURCEA35.P1, SOURCEB35.P1
unnamed: DRAINA35.P1, DRAINB35.P1, JD34.1, JD35.2, JP35.1, JS4.1, Q43.3 (D)
unnamed: GATEA35.P1, GATEB35.P1, Q43.1 (G)
unnamed: JP36.2, R44.1
unnamed: JN36.2, JS36.2, Q44.2 (S), SOURCEA36.P1, SOURCEB36.P1
unnamed: DRAINA36.P1, DRAINB36.P1, JD35.1, JD36.2, JP36.1, JS5.1, Q44.3 (D)
unnamed: GATEA36.P1, GATEB36.P1, Q44.1 (G)
unnamed: JP37.2, R45.1
unnamed: JN37.2, JS37.2, Q45.2 (S), SOURCEA37.P1, SOURCEB37.P1
unnamed: DRAINA37.P1, DRAINB37.P1, JD36.1, JD37.2, JP37.1, JS21.1, Q45.3 (D)
unnamed: GATEA37.P1, GATEB37.P1, Q45.1 (G)
unnamed: JP38.2, R46.1
unnamed: JN38.2, JS38.2, Q46.2 (S), SOURCEA38.P1, SOURCEB38.P1
unnamed: DRAINA38.P1, DRAINB38.P1, JD37.1, JD38.2, JP38.1, JS22.1, Q46.3 (D)
unnamed: GATEA38.P1, GATEB38.P1, Q46.1 (G)
unnamed: JP39.2, R47.1
unnamed: JN39.2, JS39.2, Q47.2 (S), SOURCEA39.P1, SOURCEB39.P1
unnamed: DRAINA39.P1, DRAINB39.P1, JD38.1, JD39.2, JP39.1, JS23.1, Q47.3 (D)
unnamed: GATEA39.P1, GATEB39.P1, Q47.1 (G)
unnamed: JP40.2, R48.1
unnamed: JN40.2, JS40.2, Q48.2 (S), SOURCEA40.P1, SOURCEB40.P1
unnamed: DRAINA40.P1, DRAINB40.P1, JD39.1, JD40.2, JP40.1, JS24.1, Q48.3 (D)
unnamed: GATEA40.P1, GATEB40.P1, Q48.1 (G)
unnamed: JP41.2, R49.1
unnamed: JN41.2, JS41.2, Q49.2 (S), SOURCEA41.P1, SOURCEB41.P1
unnamed: DRAINA41.P1, DRAINB41.P1, JD40.1, JD41.2, JP41.1, JS25.1, Q49.3 (D)
unnamed: GATEA41.P1, GATEB41.P1, Q49.1 (G)
unnamed: JP42.2, R50.1
unnamed: JN42.2, JS42.2, Q50.2 (S), SOURCEA42.P1, SOURCEB42.P1
unnamed: DRAINA42.P1, DRAINB42.P1, JD41.1, JD42.2, JP42.1, JS26.1, Q50.3 (D)
unnamed: GATEA42.P1, GATEB42.P1, Q50.1 (G)
unnamed: JP43.2, R51.1
unnamed: JN43.2, JS43.2, Q51.2 (S), SOURCEA43.P1, SOURCEB43.P1
unnamed: DRAINA43.P1, DRAINB43.P1, JD42.1, JD43.2, JP43.1, JS27.1, Q51.3 (D)
unnamed: GATEA43.P1, GATEB43.P1, Q51.1 (G)
unnamed: JP44.2, R52.1
unnamed: JN44.2, JS44.2, Q52.2 (S), SOURCEA44.P1, SOURCEB44.P1
unnamed: DRAINA44.P1, DRAINB44.P1, JD43.1, JD44.2, JP44.1, JS28.1, Q52.3 (D)
unnamed: GATEA44.P1, GATEB44.P1, Q52.1 (G)
unnamed: JP45.2, R53.1
unnamed: JN45.2, JS45.2, Q53.2 (S), SOURCEA45.P1, SOURCEB45.P1
unnamed: DRAINA45.P1, DRAINB45.P1, JD44.1, JD45.2, JP45.1, JS29.1, Q53.3 (D)
unnamed: GATEA45.P1, GATEB45.P1, Q53.1 (G)
unnamed: JP46.2, R54.1
unnamed: JN46.2, JS46.2, Q54.2 (S), SOURCEA46.P1, SOURCEB46.P1
unnamed: DRAINA46.P1, DRAINB46.P1, JD45.1, JD46.2, JP46.1, JS30.1, Q54.3 (D)
unnamed: GATEA46.P1, GATEB46.P1, Q54.1 (G)
unnamed: JP47.2, R55.1
unnamed: JN47.2, JS47.2, Q55.2 (S), SOURCEA47.P1, SOURCEB47.P1
unnamed: DRAINA47.P1, DRAINB47.P1, JD46.1, JD47.2, JP47.1, JS31.1, Q55.3 (D)
unnamed: GATEA47.P1, GATEB47.P1, Q55.1 (G)
unnamed: JP48.2, R56.1
unnamed: JN48.2, JS48.2, Q56.2 (S), SOURCEA48.P1, SOURCEB48.P1
unnamed: DRAINA48.P1, DRAINB48.P1, JD47.1, JD48.2, JP48.1, JS32.1, Q56.3 (D)
unnamed: GATEA48.P1, GATEB48.P1, Q56.1 (G)
unnamed: JP49.2, R57.1
unnamed: JN49.2, JS49.2, Q57.2 (S), SOURCEA49.P1, SOURCEB49.P1
unnamed: DRAINA49.P1, DRAINB49.P1, JD49.2, JP49.1, JS65.1, Q57.3 (D)
unnamed: GATEA49.P1, GATEB49.P1, Q57.1 (G)
unnamed: JP50.2, R58.1
unnamed: JN50.2, JS50.2, Q58.2 (S), SOURCEA50.P1, SOURCEB50.P1
unnamed: DRAINA50.P1, DRAINB50.P1, JD49.1, JD50.2, JP50.1, JS66.1, Q58.3 (D)
unnamed: GATEA50.P1, GATEB50.P1, Q58.1 (G)
unnamed: JP51.2, R59.1
unnamed: JN51.2, JS51.2, Q59.2 (S), SOURCEA51.P1, SOURCEB51.P1
unnamed: DRAINA51.P1, DRAINB51.P1, JD50.1, JD51.2, JP51.1, JS67.1, Q59.3 (D)
unnamed: GATEA51.P1, GATEB51.P1, Q59.1 (G)
unnamed: JP52.2, R60.1
unnamed: JN52.2, JS52.2, Q60.2 (S), SOURCEA52.P1, SOURCEB52.P1
unnamed: DRAINA52.P1, DRAINB52.P1, JD51.1, JD52.2, JP52.1, JS68.1, Q60.3 (D)
unnamed: GATEA52.P1, GATEB52.P1, Q60.1 (G)
unnamed: JP53.2, R61.1
unnamed: JN53.2, JS53.2, Q61.2 (S), SOURCEA53.P1, SOURCEB53.P1
unnamed: DRAINA53.P1, DRAINB53.P1, JD52.1, JD53.2, JP53.1, JS69.1, Q61.3 (D)
unnamed: GATEA53.P1, GATEB53.P1, Q61.1 (G)
unnamed: JP54.2, R62.1
unnamed: JN54.2, JS54.2, Q62.2 (S), SOURCEA54.P1, SOURCEB54.P1
unnamed: DRAINA54.P1, DRAINB54.P1, JD53.1, JD54.2, JP54.1, JS70.1, Q62.3 (D)
unnamed: GATEA54.P1, GATEB54.P1, Q62.1 (G)
unnamed: JP55.2, R63.1
unnamed: JN55.2, JS55.2, Q63.2 (S), SOURCEA55.P1, SOURCEB55.P1
unnamed: DRAINA55.P1, DRAINB55.P1, JD54.1, JD55.2, JP55.1, JS71.1, Q63.3 (D)
unnamed: GATEA55.P1, GATEB55.P1, Q63.1 (G)
unnamed: JP56.2, R64.1
unnamed: JN56.2, JS56.2, Q64.2 (S), SOURCEA56.P1, SOURCEB56.P1
unnamed: DRAINA56.P1, DRAINB56.P1, JD55.1, JD56.2, JP56.1, JS72.1, Q64.3 (D)
unnamed: GATEA56.P1, GATEB56.P1, Q64.1 (G)
unnamed: JP57.2, R65.1
unnamed: JN57.2, JS57.2, Q65.2 (S), SOURCEA57.P1, SOURCEB57.P1
unnamed: DRAINA57.P1, DRAINB57.P1, JD56.1, JD57.2, JP57.1, JS73.1, Q65.3 (D)
unnamed: GATEA57.P1, GATEB57.P1, Q65.1 (G)
unnamed: JP58.2, R66.1
unnamed: JN58.2, JS58.2, Q66.2 (S), SOURCEA58.P1, SOURCEB58.P1
unnamed: DRAINA58.P1, DRAINB58.P1, JD57.1, JD58.2, JP58.1, JS74.1, Q66.3 (D)
unnamed: GATEA58.P1, GATEB58.P1, Q66.1 (G)
unnamed: JP59.2, R67.1
unnamed: JN59.2, JS59.2, Q67.2 (S), SOURCEA59.P1, SOURCEB59.P1
unnamed: DRAINA59.P1, DRAINB59.P1, JD58.1, JD59.2, JP59.1, JS75.1, Q67.3 (D)
unnamed: GATEA59.P1, GATEB59.P1, Q67.1 (G)
unnamed: JP60.2, R68.1
unnamed: JN60.2, JS60.2, Q68.2 (S), SOURCEA60.P1, SOURCEB60.P1
unnamed: DRAINA60.P1, DRAINB60.P1, JD59.1, JD60.2, JP60.1, JS76.1, Q68.3 (D)
unnamed: GATEA60.P1, GATEB60.P1, Q68.1 (G)
unnamed: JP61.2, R69.1
unnamed: JN61.2, JS61.2, Q69.2 (S), SOURCEA61.P1, SOURCEB61.P1
unnamed: DRAINA61.P1, DRAINB61.P1, JD60.1, JD61.2, JP61.1, JS77.1, Q69.3 (D)
unnamed: GATEA61.P1, GATEB61.P1, Q69.1 (G)
unnamed: JP62.2, R70.1
unnamed: JN62.2, JS62.2, Q70.2 (S), SOURCEA62.P1, SOURCEB62.P1
unnamed: DRAINA62.P1, DRAINB62.P1, JD61.1, JD62.2, JP62.1, JS78.1, Q70.3 (D)
unnamed: GATEA62.P1, GATEB62.P1, Q70.1 (G)
unnamed: JP63.2, R71.1
unnamed: JN63.2, JS63.2, Q71.2 (S), SOURCEA63.P1, SOURCEB63.P1
unnamed: DRAINA63.P1, DRAINB63.P1, JD62.1, JD63.2, JP63.1, JS79.1, Q71.3 (D)
unnamed: GATEA63.P1, GATEB63.P1, Q71.1 (G)
unnamed: JP64.2, R72.1
unnamed: JN64.2, JS64.2, Q72.2 (S), SOURCEA64.P1, SOURCEB64.P1
unnamed: DRAINA64.P1, DRAINB64.P1, JD63.1, JD64.2, JP64.1, JS80.1, Q72.3 (D)
unnamed: GATEA64.P1, GATEB64.P1, Q72.1 (G)
unnamed: JP65.2, R73.1
unnamed: JN65.2, JS65.2, Q73.2 (S), SOURCEA65.P1, SOURCEB65.P1
unnamed: DRAINA65.P1, DRAINB65.P1, JD65.2, JP65.1, JS81.1, Q73.3 (D)
unnamed: GATEA65.P1, GATEB65.P1, Q73.1 (G)
unnamed: JP66.2, R74.1
unnamed: JN66.2, JS66.2, Q74.2 (S), SOURCEA66.P1, SOURCEB66.P1
unnamed: DRAINA66.P1, DRAINB66.P1, JD65.1, JD66.2, JP66.1, JS82.1, Q74.3 (D)
unnamed: GATEA66.P1, GATEB66.P1, Q74.1 (G)
unnamed: JP67.2, R79.1
unnamed: JN67.2, JS67.2, Q75.2 (S), SOURCEA67.P1, SOURCEB67.P1
unnamed: DRAINA67.P1, DRAINB67.P1, JD66.1, JD67.2, JP67.1, JS83.1, Q75.3 (D)
unnamed: GATEA67.P1, GATEB67.P1, Q75.1 (G)
unnamed: JP68.2, R80.1
unnamed: JN68.2, JS68.2, Q76.2 (S), SOURCEA68.P1, SOURCEB68.P1
unnamed: DRAINA68.P1, DRAINB68.P1, JD67.1, JD68.2, JP68.1, JS84.1, Q76.3 (D)
unnamed: GATEA68.P1, GATEB68.P1, Q76.1 (G)
unnamed: JP69.2, R83.1
unnamed: JN69.2, JS69.2, Q77.2 (S), SOURCEA69.P1, SOURCEB69.P1
unnamed: DRAINA69.P1, DRAINB69.P1, JD68.1, JD69.2, JP69.1, JS85.1, Q77.3 (D)
unnamed: GATEA69.P1, GATEB69.P1, Q77.1 (G)
unnamed: JP70.2, R84.1
unnamed: JN70.2, JS70.2, Q78.2 (S), SOURCEA70.P1, SOURCEB70.P1
unnamed: DRAINA70.P1, DRAINB70.P1, JD69.1, JD70.2, JP70.1, JS86.1, Q78.3 (D)
unnamed: GATEA70.P1, GATEB70.P1, Q78.1 (G)
unnamed: JP71.2, R87.1
unnamed: JN71.2, JS71.2, Q79.2 (S), SOURCEA71.P1, SOURCEB71.P1
unnamed: DRAINA71.P1, DRAINB71.P1, JD70.1, JD71.2, JP71.1, JS87.1, Q79.3 (D)
unnamed: GATEA71.P1, GATEB71.P1, Q79.1 (G)
unnamed: JP72.2, R88.1
unnamed: JN72.2, JS72.2, Q80.2 (S), SOURCEA72.P1, SOURCEB72.P1
unnamed: DRAINA72.P1, DRAINB72.P1, JD71.1, JD72.2, JP72.1, JS88.1, Q80.3 (D)
unnamed: GATEA72.P1, GATEB72.P1, Q80.1 (G)
unnamed: JP73.2, R91.1
unnamed: JN73.2, JS73.2, Q81.2 (S), SOURCEA73.P1, SOURCEB73.P1
unnamed: DRAINA73.P1, DRAINB73.P1, JD72.1, JD73.2, JP73.1, JS89.1, Q81.3 (D)
unnamed: GATEA73.P1, GATEB73.P1, Q81.1 (G)
unnamed: JP74.2, R92.1
unnamed: JN74.2, JS74.2, Q82.2 (S), SOURCEA74.P1, SOURCEB74.P1
unnamed: DRAINA74.P1, DRAINB74.P1, JD73.1, JD74.2, JP74.1, JS90.1, Q82.3 (D)
unnamed: GATEA74.P1, GATEB74.P1, Q82.1 (G)
unnamed: JP75.2, R95.1
unnamed: JN75.2, JS75.2, Q83.2 (S), SOURCEA75.P1, SOURCEB75.P1
unnamed: DRAINA75.P1, DRAINB75.P1, JD74.1, JD75.2, JP75.1, JS91.1, Q83.3 (D)
unnamed: GATEA75.P1, GATEB75.P1, Q83.1 (G)
unnamed: JP76.2, R96.1
unnamed: JN76.2, JS76.2, Q84.2 (S), SOURCEA76.P1, SOURCEB76.P1
unnamed: DRAINA76.P1, DRAINB76.P1, JD75.1, JD76.2, JP76.1, JS92.1, Q84.3 (D)
unnamed: GATEA76.P1, GATEB76.P1, Q84.1 (G)
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
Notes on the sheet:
NMOS Logic Transistor Cell
